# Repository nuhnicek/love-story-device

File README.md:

# GSM touch keychain (pair)

Press the button on one keychain and the other one vibrates and blinks, over 2G (SIM800L).

**Newest design: [`v3/`](v3/README.md)**, one custom 23 × 30 mm board with the nRF9151 (LTE-M), hand assembled.

**Module build: [`v2/`](v2/README.md)**, the module build: XIAO ESP32-C3 + SIM800L + 802530 LiPo, no custom PCB.
It has the parts list, schematic, case STLs/G-code and the relay backend.

v1 (custom PCB, ATtiny85):

- `hardware/` — carrier PCB (KiCad 10), parts list, cost estimate, gerbers, assembly files. Start at [hardware/README.md](hardware/README.md).
- `firmware/` — ATtiny85 firmware (1NCE GPRS → relay server), host unit tests.
- `server/` — relay server (Python, no dependencies) + tests + fake keychain for bring-up.
- `enclosure/` — 3D-printed case (OpenSCAD), heart perfboard layout, STLs and ready-to-print
  Ender-3 V2/Pro G-code.
- `.mcp.json` — project-scoped KiCad MCP servers (`mcp-server-kicad`: PCB + project tools).

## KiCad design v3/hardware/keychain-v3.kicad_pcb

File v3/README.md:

# GSM touch keychain, v3: one custom board with the nRF9151 (LTE-M)

v3 puts everything on **one 30 × 50 mm board** built around the **Nordic nRF9151**, including a
**heart of 18 RGB LEDs** and **programming over USB-C**. That
single chip holds the processor and the LTE-M/NB-IoT modem. There's no XIAO and no SIM800L,
and it's not affected by the 2G shutdown. You assemble it yourself.

| | v2 (modules) | **v3 (this)** |
|---|---|---|
| Network | 2G (SIM800L), ends for 1NCE ~end of 2027 | **LTE-M / NB-IoT** (4G), no 2G shutdown problem |
| Electronics | XIAO + SIM800L stacked, ~31 × 27 × 10 mm | **one 30 × 50 × ~4.5 mm board** with the RGB heart on it (USB-C is the tallest part) |
| Modem idle | ~1 mA (2G) | **µA level** with LTE-M power saving (PSM 2.7 µA, eDRX ~18 µA per Nordic) |
| Assembly | wires + through-hole | SMD: solder paste + stencil + hot plate (details below) |

**Guides:**
- [PROGRAMMING.md](PROGRAMMING.md): the first flash with a €5 Raspberry Pi Pico as the SWD probe (wiring + pyOCD), then updates over USB-C.
- [TESTING.md](TESTING.md): step-by-step checks of a freshly soldered board on the labelled test pads (bottom side), with the expected value at every pad.

## Files (`hardware/`)

| File | |
|---|---|
| `fab/schematic.pdf` | Schematic (A3). KiCad 10 project `keychain-v3.kicad_pro` |
| `keychain-v3.kicad_pcb` | The board: **4 layers, 1.0 mm**. ERC, DRC and schematic↔PCB parity are clean |
| `fab/keychain-v3-gerbers.zip` | **Upload this to JLCPCB** (all 4 copper layers, paste layers for the stencil, drills) |
| `fab/assembly-top.pdf`, `assembly-bottom.pdf` | Where every part goes, for hand placement |
| `fab/keychain-v3-pos-top.csv` | Part positions (only needed for machine assembly) |
| `BOM.md`, `fab/keychain-v3-bom.csv` | Parts list with suggested part numbers |
| `fab/keychain-v3.step`, `render-*.png` | 3D model for the case, pictures |
| `scripts/make_all.sh` | Regenerates everything: schematic → PCB → routing → checks → fab files |

## What's on the board

- **nRF9151** (U1):
  - Battery straight to VDD through a ferrite bead; no regulator needed (3.0–5.5 V).
  - The support parts follow Nordic's reference and the open-source Makerdiary nRF9151
    Connect Kit (CC BY-SA 4.0): 10 µF + 1 µF on VDD, 10 k ENABLE pull-up, 4.7 µF on DEC0,
    100 nF + 4.7 µF on VDD_GPIO, 1 k + 100 nF on reset.
- **3.0 V for the I/O pins** (U3, XC6206, 1 µA). It follows the battery up and down, which is the power-up order the nRF9151 requires.
- **Charger** (U2, TP4054) on USB-C:
  - **213 mA** (R3 = 4.7 k), which suits a 200–500 mAh cell. Use 3.3 k for 300 mA if the cell is at least 300 mAh.
  - "USB plugged in" goes to P0.31 (VBUS/2); with the battery voltage the firmware knows when it's charging.
- **Battery voltage** is measured by the modem itself (`AT%XVBAT`), so there are no divider resistors.
- **Nano-SIM** (J3, hinged holder on the bottom), with the ESD protection the SIM interface requires (U4).
  - U4 sits directly above the SIM contacts, as ESD protection should; its 100 nF (C13) is on the bottom next to the holder.
  - The nRF9151 runs SIMs at 1.8 V; 1NCE SIMs support that.
- **Antenna:**
  - A 50 Ω trace runs straight from the antenna pin to a **U.FL** socket.
  - It goes through a 0 Ω resistor and two unfitted pads (C14/C15) for later tuning.
  - Ground stitching vias around the socket; the 2nd layer is solid ground.
- **Motor:** AO3400A + flyback diode, the same as v1/v2, wired to the MOT+/− pads.
- **RGB heart (on the board):**
  - 18 × **Würth 1312020030000** (WL-ICLED, 2.0 × 2.0 mm, WS2812 protocol), each with its own 100 nF.
    - They sit on a 26 × 14 mm heart curve at the top of the board.
    - The parts are upright, evenly spaced and at least 0.3 mm apart. 18 is the most that fits on a 30 mm wide board; with 20, pads would touch on the curves.
    - In stock at DigiKey. Alternative: Dialight 587-1024-147F.
  - The load switch (U6, TPS22917) and the data buffer (U7, SN74LV1T34) sit inside the heart.
    - U6 cuts the LED power when they're dark. These LEDs draw ~1 mA each even when off, which would cost more than the whole keychain in standby.
    - U7 lifts the 3.0 V data to the LED supply.
  - The LEDs are fed by a heart-shaped copper plane on layer 3.
  - The data chain runs on the bottom layer, with a few links on top. Every link is collision-checked.
  - Any colour per LED and fades.
    - The LEDs are rated down to 3.3 V, so expect full colour down to ~3.3 V battery.
    - They take 5.5 mA per colour, so the whole heart at full white is ≈ 300 mA. The small LiPo handles that in short flashes.
  - Firmware: Zephyr `ws2812` driver with a reset time of ≥ 280 µs and a "1" pulse of ≈ 0.9 µs. The Würth datasheet allows 0.75–1.05 µs.
- **USB-C with data (CP2102N, U5):**
  - Firmware updates and the log go over USB-C. The SWD pads are needed only once, to install the bootloader.
  - The PC can reset the board through DTR/RTS (Q2, as on ESP32 boards). Idle, an open port and an unplugged cable never reset it.
  - The chip runs only from USB, so it costs no battery.
- **Side button** (SW1) on the right edge, pressed through the case's flexing tab.
- **Pads on the bottom:**
  - BAT+/−, MOT+/−;
  - **SWD** (CK, IO, RST, VT, GND), for the one-time bootloader flash.

Pins used: P0.05 motor PWM, P0.06 LED data, P0.19 LED power, P0.30 button, P0.31 USB plugged in, P0.24 UART TX, P0.25 UART RX (to the USB-serial chip)
(set these in the Zephyr devicetree; the nRF9151 can put the UART on any pin).

## Ordering

**PCB (JLCPCB):** upload `fab/keychain-v3-gerbers.zip` and choose:
- **4 layers, 1.0 mm**, impedance stack-up **JLC04101H-7628**. The antenna trace is sized for it (0.35 mm over layer 2). Check it in JLC's impedance calculator.
- **Surface finish: ENIG.** It isn't optional here: a flat finish matters for the nRF9151's pads underneath, and HASL is too uneven.
- Via covering: tented. Silkscreen: any colour.
- **Stencil:** order one with the PCB, **top side only, 0.10 mm thick**, framework-less is fine.

**Parts:** see `BOM.md`; LCSC, TME, Mouser or DigiKey all work. Order for **3 boards**, plus extra small parts.
- The **nRF9151-LACA** is the expensive part. It's sold as cut tape by DigiKey, Mouser and TME. Check the price; plan roughly €20–30 each.
- It's moisture sensitive (MSL 3): keep it in its sealed bag until you solder.

**Rough cost for a pair (+1 spare board):**

| Item | Approx. |
|---|---|
| PCB 4-layer ENIG × 5 + stencil + shipping to CZ | ~€35–60 |
| 3 × nRF9151 | ~€60–90 |
| Other parts for 3 boards (USB-C, SIM holder, U.FL, CP2102N, 30 RGB LEDs, ICs, passives) | ~€30–45 |
| 2 × LTE FPC antenna with U.FL | ~€5–20 |
| 2 × LiPo, 2 × motor, heart parts | ~€10–15 |
| 2 × 1NCE SIM | ~€24 |
| **Total** | **≈ €165–250 (≈ 4 100–6 200 Kč)** |

This is more than v2. You pay for the nRF9151 and a 4-layer ENIG board, and get LTE-M, much
lower standby current and a smaller keychain.

## Hand assembly

You need:
- **Hot plate**, about €25–40. Hot air works too, but a hot plate is easier for the nRF9151.
- **Solder paste:** Sn63/Pb37, the easiest to work with; or low-temperature paste.
- **Flux, fine tweezers,** a loupe or microscope, a multimeter, and isopropyl alcohol.
- **Current-limited bench supply** (optional, but very useful for the first power-up).

1. **Paste:**
   - Tape the board down with spare boards or scrap of the same thickness around it.
   - Line up the stencil and spread the paste in one stroke.
   - Check that every pad of the nRF9151, including the big centre ones, got paste.
2. **Place parts:**
   - Follow `assembly-top.pdf`. Start with the **nRF9151**, matching its pin-1 corner to the triangle on the silkscreen.
   - Then U2/U3/U4/Q1. Watch U4: it's tiny, and pin 1 has a dot.
   - Then the passives, USB-C, U.FL and SW1.
   - **Leave C14/C15 empty.**
3. **Reflow on the hot plate:**
   - Heat to ~150 °C for about a minute, then to the paste's peak: ~215–225 °C for Sn63, ~245 °C for lead-free.
   - Hold until all the paste has turned shiny, plus ~20 s.
   - Then slide the board off onto a metal surface.
   - Don't nudge the nRF9151 while hot: it self-centres on its pads.
4. **Inspect:**
   - Check for bridges on the USB-C, U2 and U4 with a loupe; fix them with flux + iron + solder wick.
   - You can't see under the nRF9151, so test it electrically (step 6).
5. **Bottom side, with an iron:**
   - The **SIM holder**: its contacts are on the outer edge, and the 4 shield tabs are at its sides.
   - C13 (100 nF, 0603) next to the holder.
   - Then the wires to the battery and the motor.
6. **First power-up, before connecting a battery:**
   - Put **3.8 V** on BAT+/− from a supply limited to ~100 mA. Idle current should be a few mA or less, with nothing getting warm.
   - **VT** should read **3.0 V**.
   - Then plug in USB-C: about 213 mA should flow into a battery.
7. **First flash, once, over SWD:**
   - Connect a debug probe to **CK/IO/RST/VT/GND**: a J-Link, the debug-out of an nRF9151 DK, or a borrowed / €5 Pico probe with pyOCD.
   - Flash the **MCUboot** bootloader together with the first app.
   - MCUboot is set to wait ~0.5 s after every reset for an update over the USB serial port.
8. **From then on, over USB-C only:**
   - The board shows up as a USB serial port (CP2102N). Log: any serial terminal at 115200.
   - Update: `mcumgr --conntype serial --connstring "dev=<port>,baud=115200" image upload app.bin`, then `reset`.
   - The PC resets the board by setting DTR high and RTS low. A small script in the firmware folder will do this.
   - LTE-M test: the `at_client` sample over USB, `AT+CFUN=1`, then `AT+CEREG?`. Registration status 1 or 5 means LTE-M works with the 1NCE SIM.

## Design review (2026-11-25)

DRC only proves the geometry is legal, so the board was also checked for design mistakes.
Found and fixed:

| Problem | Fix |
|---|---|
| Wide-track rules didn't apply to the nRF9151 supply and the motor line: the schematic names those nets `/VDD_NRF` and `/MOT_N`. VDD was routed 0.11 mm wide over 34 mm and 3 layers; the motor line went down to 0.09 mm | Rules match the real net names. VDD: 0.3 mm on the top layer only, fixed short track from pin 14 to C5/C6. Motor: 0.3 mm |
| Side button rotated the wrong way: actuator into the board, pads at the edge | Rotated 180°; the actuator now sticks 0.24 mm out of the right edge |
| Charger input and output caps (C1/C2) were 8.5 mm from the TP4054 | Charger block moved next to the battery pads; caps 2.7 and 4 mm from the pins |
| Signal and power vias under the nRF9151 | Keep-out while routing: only ground vias under the SiP, and layer 2 is solid ground there |
| SIM ESD (U4) and its 100 nF sat by the SiP, far from the SIM contacts | U4 moved directly above the contacts, with fixed short runs to each contact. The 100 nF is on the bottom next to the VCC contact |
| Several caps had their signal pad on the far side (C5, C6, C9, C10, C12) | Rotated; DEC0 cap 1.6 mm and VDD_GPIO 100 nF 1.9 mm from their pins |
| The two unfitted antenna pads would have got solder paste | Own footprint without stencil openings |
| Alternative charger part: the MCP73831 drives its status pin to 5 V, which would damage the nRF9151's 3.0 V pin | BOM now names the MCP73832 (open-drain status) |
| The left side of the SiP was too crowded to route cleanly | Board 2 mm wider. UART moved to P0.24/P0.25 and the debug pads put in pin order |

Checked and OK:
- every part's pinout against its footprint;
- the nRF9151 reference circuit;
- the USB-C front at the board edge;
- the RF path (no other copper near it, ground under and around it);
- the SIM holder's keep-out areas;
- 1.0 mm 4-layer stack-up, 0.3/0.6 mm vias, minimum track 0.11 mm (JLC 4-layer allows 0.09).

### Added after the review: USB programming and the RGB heart (2026-11-26)

- **USB corner:** laid out by pin order.
  - The CP2102N sits between the antenna socket and the button.
  - The reset transistor sits at its DTR/RTS pins; its caps and dividers sit at their pins.
- **Fixed routing:** the USB data pair is a fixed pair on layer 3, joined under the connector body so both plug orientations work.
- **Heart:** the LED chain runs on the bottom layer under the heart, and the LED supply is a plane on layer 3.
- **Hand-routed nets:** the SIM lines, reset, enable, the battery feed to the regulator and the LED data were drawn as fixed tracks, so the result doesn't depend on autorouter luck.
- **Charge status (CHRG):** dropped; the firmware uses *USB plugged in* plus the battery voltage instead.
- **Result:** ERC, DRC and schematic↔PCB parity are clean. The board is 30 × 50 mm and has 89 parts.
- **Test pads (added 2026-11-26):**
  - 12 labelled 0.9 mm pads on the bottom: 5V, V3U, DET, PRG, VDD, SIM, VLED, GATE, LED, BTN and 2 × GND.
  - Each one is wired with a fixed, collision-checked stub, so they don't depend on the autorouter.
  - See [TESTING.md](TESTING.md).

## Status and open points

- **Firmware: not written yet.**
  - v3 needs a Zephyr / nRF Connect SDK version of the keychain firmware.
  - The protocol (`firmware/keychain/protocol.h`) and the relay server (`v2/backend`) stay the same.
  - LTE-M power saving (eDRX) decides how fast incoming taps arrive (a few seconds to ~20 s) and how long the battery lasts. That gets tuned on the real board.
- **Modem firmware:** check the version with `AT%SHORTSWVER`. A brand-new chip already has modem firmware; later updates go through the app or `nrfutil` with a J-Link.
- **Antenna:**
  - LTE-M uses 800/900 MHz in Czechia, and antennas for those bands want length. A small flexible antenna inside a keychain will work, with reduced range.
  - Use the biggest one that fits; tuning with C14/C15 needs a network analyser.
- **1NCE LTE-M in Czechia** probably runs via T-Mobile CZ, but that isn't confirmed. Test one SIM first, e.g. on an M5Stamp CatM or an nRF9151 dev kit.
- **First build:**
  - This is a new design and hasn't been made yet. Order the spare SiP.
  - Hand-soldering an LGA chip is the hardest step, so expect one board to need rework.
- **Case:** not yet adapted to v3. Once you've picked the battery, the case can be redrawn around the 30 × 50 mm board: thinner than v2, with the heart under a translucent lid or light holes.

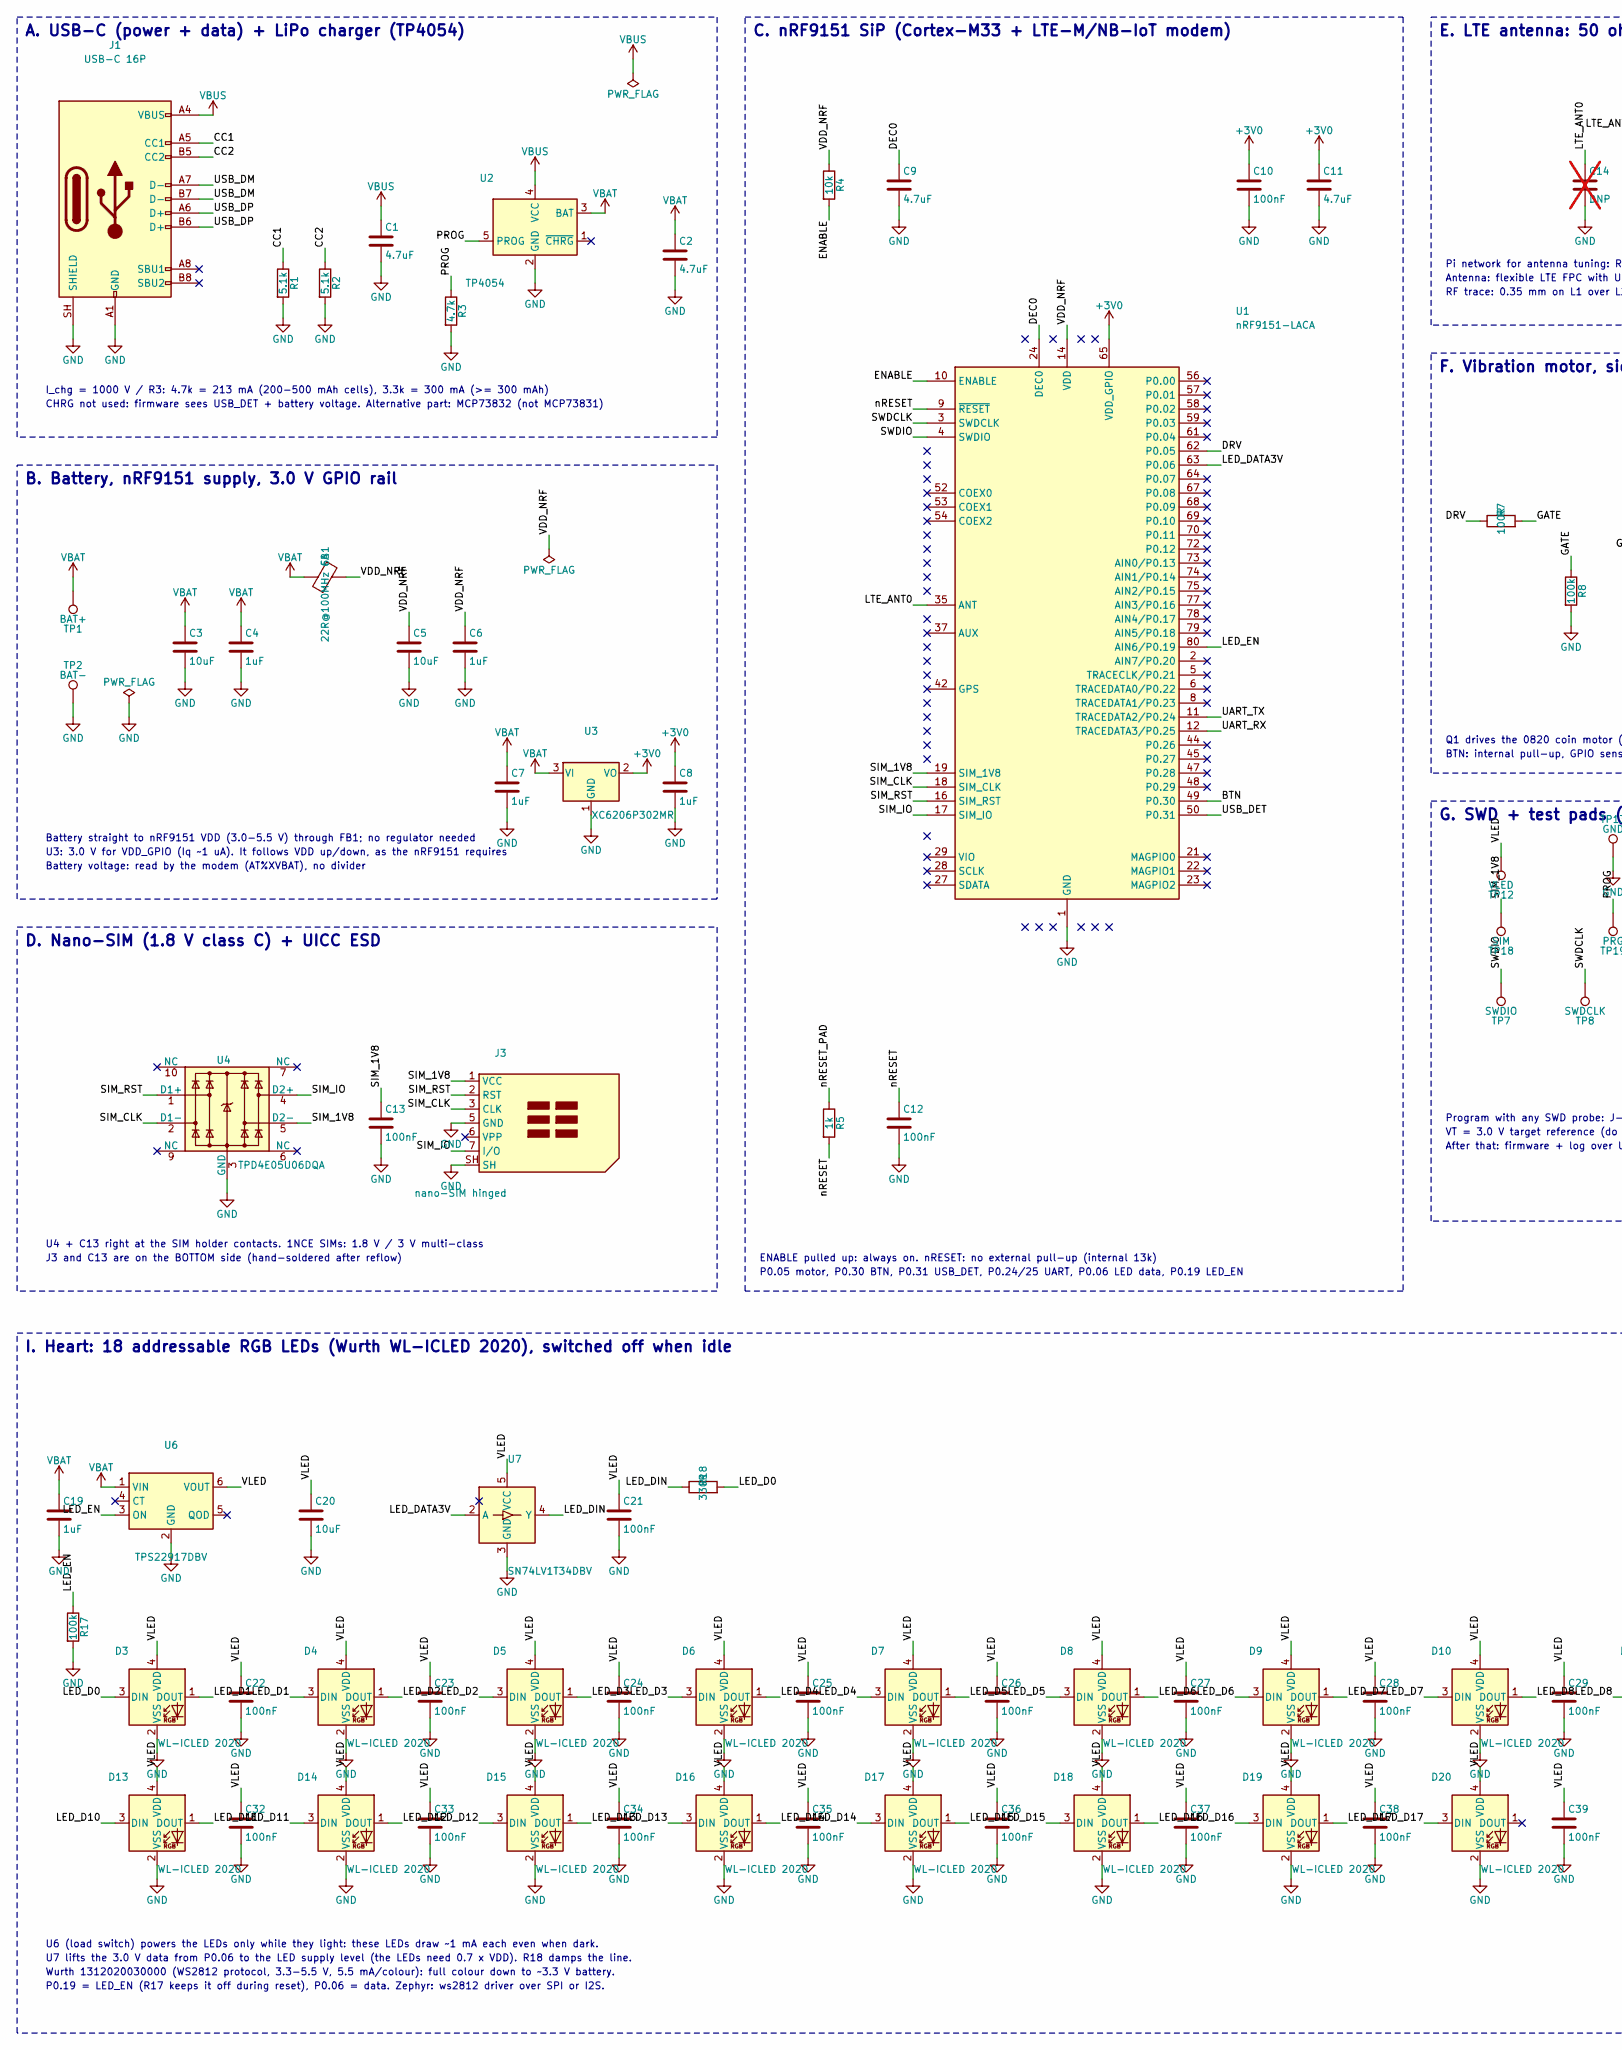
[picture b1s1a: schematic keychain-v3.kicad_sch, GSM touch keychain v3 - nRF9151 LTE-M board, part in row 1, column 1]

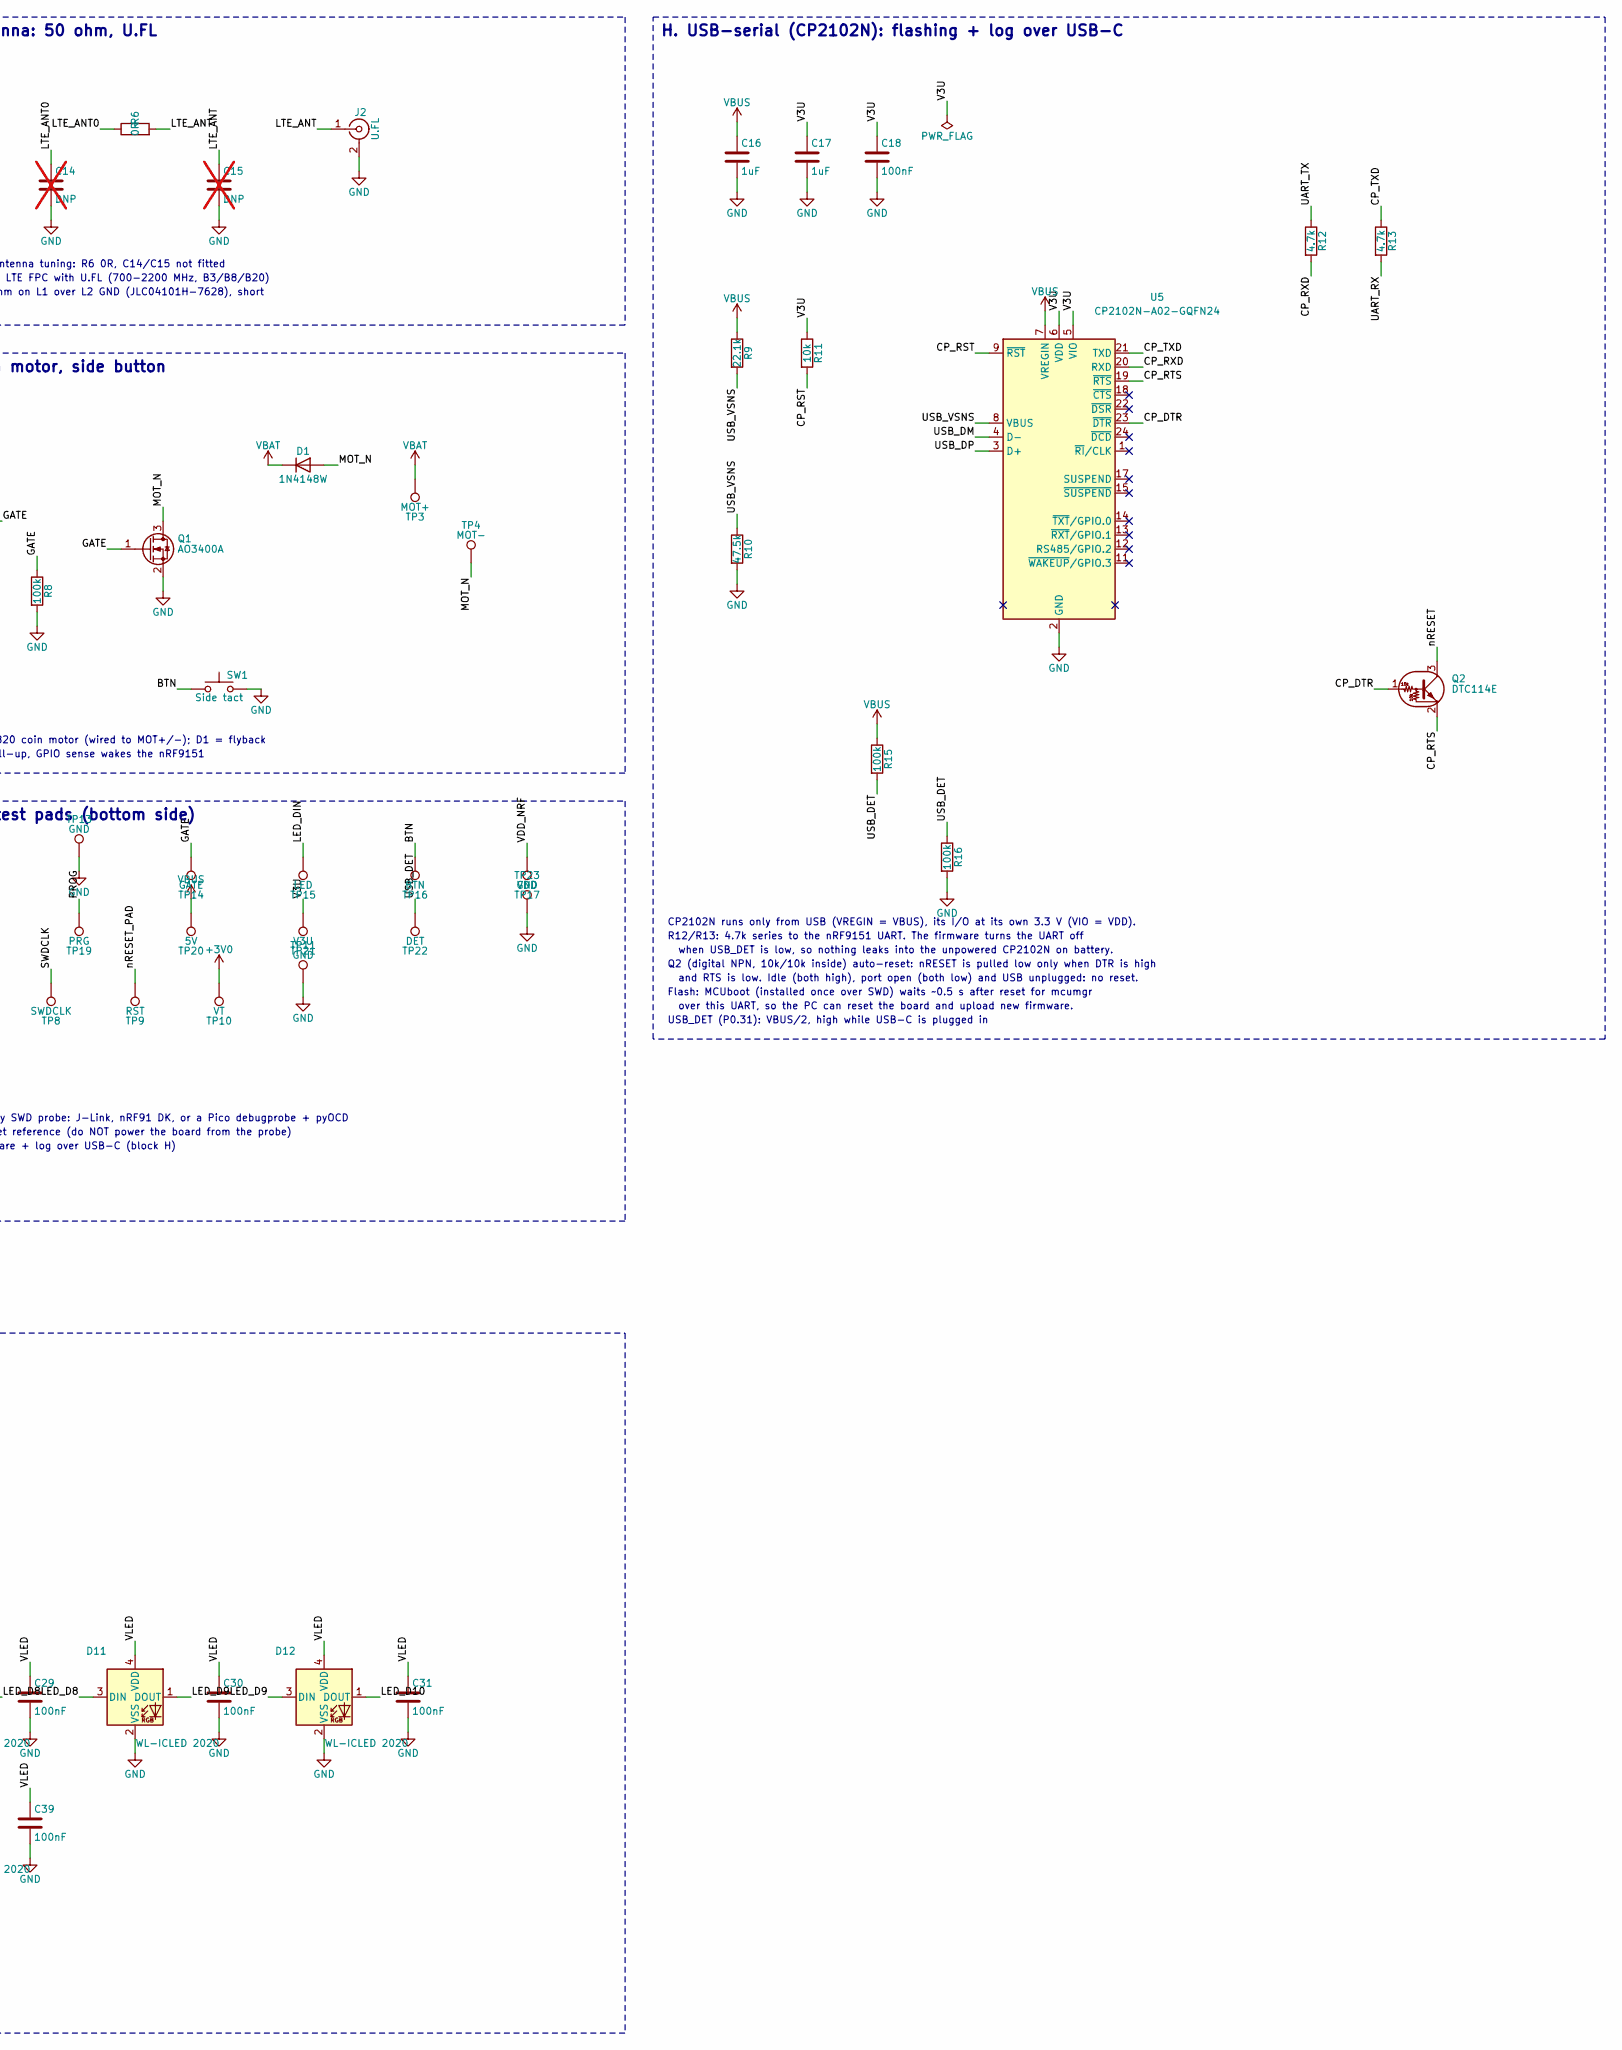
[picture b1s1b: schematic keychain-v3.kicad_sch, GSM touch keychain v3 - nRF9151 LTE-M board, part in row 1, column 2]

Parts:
C1, C2, C9, C11: 4.7uF; C_0603_1608Metric
C3, C5, C20: 10uF; C_0603_1608Metric
C4, C6, C7, C8: 1uF; C_0603_1608Metric
C10, C12, C13: 100nF; C_0603_1608Metric
C14, C15: DNP; C_0402_NoPaste; not fitted
C16, C17, C19: 1uF; C_0402_1005Metric
C18, C21, C22, C23, C24, C25, C26, C27, C28, C29, C30, C31, C32, C33, C34, C35, C36, C37, C38, C39: 100nF; C_0402_1005Metric
D1: 1N4148W; D_SOD-123
D3, D4, D5, D6, D7, D8, D9, D10, D11, D12, D13, D14, D15, D16, D17, D18, D19, D20: WL-ICLED 2020; LED_WL-ICLED_2020
FB1: 22R@100MHz 6A; L_0805_2012Metric
J1: USB-C 16P; USB_C_Receptacle_GCT_USB4105-xx-A_16P_TopMnt_Horizontal
J2: U.FL; U.FL_Hirose_U.FL-R-SMT-1_Vertical
J3: nano-SIM hinged; nanoSIM_GCT_SIM8060-6-0-14-00
Q1: AO3400A; SOT-23
Q2: DTC114E; SOT-23
R1, R2: 5.1k; R_0402_1005Metric
R3, R12, R13: 4.7k; R_0402_1005Metric
R4: 10k; R_0603_1608Metric
R5: 1k; R_0603_1608Metric
R6: 0R; R_0402_1005Metric
R7: 100R; R_0603_1608Metric
R8: 100k; R_0603_1608Metric
R9: 22.1k; R_0402_1005Metric
R10: 47.5k; R_0402_1005Metric
R11: 10k; R_0402_1005Metric
R15, R16, R17: 100k; R_0402_1005Metric
R18: 330R; R_0402_1005Metric
SW1: Side tact; SW_Push_1P1T-MP_NO_Horizontal_Alps_SKRTLAE010
TP1: BAT+; WirePad_1.5mm
TP2: BAT-; WirePad_1.5mm
TP3: MOT+; WirePad_1.0mm
TP4: MOT-; WirePad_1.0mm
TP7: SWDIO; WirePad_0.9mm
TP8: SWDCLK; WirePad_0.9mm
TP9: RST; WirePad_0.9mm
TP10: VT; WirePad_0.9mm
TP11, TP13, TP23: GND; WirePad_0.9mm
TP12: VLED; WirePad_0.9mm
TP14: GATE; WirePad_0.9mm
TP15: LED; WirePad_0.9mm
TP16: BTN; WirePad_0.9mm
TP17: VDD; WirePad_0.9mm
TP18: SIM; WirePad_0.9mm
TP19: PRG; WirePad_0.9mm
TP20: 5V; WirePad_0.9mm
TP21: V3U; WirePad_0.9mm
TP22: DET; WirePad_0.9mm
U1: nRF9151-LACA; Nordic_nRF9151-LAxx_LGA-80-33EP_12.1x11.1mm_P0.5mm
U2: TP4054; SOT-23-5
U3: XC6206P302MR; SOT-23-3
U4: TPD4E05U06DQA; USON-10_2.5x1.0mm_P0.5mm
U5: CP2102N-A02-GQFN24; QFN-24-1EP_4x4mm_P0.5mm_EP2.6x2.6mm
U6: TPS22917DBV; SOT-23-6
U7: SN74LV1T34DBV; SOT-23-5

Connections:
+3V0: C8.1, C10.1, C11.1, TP10.1, U1.65 (VDD_GPIO), U3.2 (VO)
/BTN: SW1.1, TP16.1, U1.49 (P0.30)
/CC1: J1.A5 (CC1), R1.1
/CC2: J1.B5 (CC2), R2.1
/CP_DTR: Q2.1 (B), U5.23 (~DTR)
/CP_RST: R11.2, U5.9 (~RST)
/CP_RTS: Q2.2 (E), U5.19 (~RTS)
/CP_RXD: R12.2, U5.20 (RXD)
/CP_TXD: R13.1, U5.21 (TXD)
/DEC0: C9.1, U1.24 (DEC0)
/DRV: R7.1, U1.62 (P0.05)
/ENABLE: R4.2, U1.10 (ENABLE)
/GATE: Q1.1 (G), R7.2, R8.1, TP14.1
/LED_D0: D3.3 (DIN), R18.2
/LED_D1: D3.1 (DOUT), D4.3 (DIN)
/LED_D2: D4.1 (DOUT), D5.3 (DIN)
/LED_D3: D5.1 (DOUT), D6.3 (DIN)
/LED_D4: D6.1 (DOUT), D7.3 (DIN)
/LED_D5: D7.1 (DOUT), D8.3 (DIN)
/LED_D6: D8.1 (DOUT), D9.3 (DIN)
/LED_D7: D9.1 (DOUT), D10.3 (DIN)
/LED_D8: D10.1 (DOUT), D11.3 (DIN)
/LED_D9: D11.1 (DOUT), D12.3 (DIN)
/LED_D10: D12.1 (DOUT), D13.3 (DIN)
/LED_D11: D13.1 (DOUT), D14.3 (DIN)
/LED_D12: D14.1 (DOUT), D15.3 (DIN)
/LED_D13: D15.1 (DOUT), D16.3 (DIN)
/LED_D14: D16.1 (DOUT), D17.3 (DIN)
/LED_D15: D17.1 (DOUT), D18.3 (DIN)
/LED_D16: D18.1 (DOUT), D19.3 (DIN)
/LED_D17: D19.1 (DOUT), D20.3 (DIN)
/LED_DATA3V: U1.63 (P0.06), U7.2 (A)
/LED_DIN: R18.1, TP15.1, U7.4 (Y)
/LED_EN: R17.1, U1.80 (AIN6/P0.19), U6.3 (ON)
/LTE_ANT: C15.1, J2.1 (In), R6.2
/LTE_ANT0: C14.1, R6.1, U1.35 (ANT)
/MOT_N: D1.2 (A), Q1.3 (D), TP4.1
/PROG: R3.1, TP19.1, U2.5 (PROG)
/SIM_1V8: C13.1, J3.1 (VCC), TP18.1, U1.19 (SIM_1V8), U4.5 (D2-)
/SIM_CLK: J3.3 (CLK), U1.18 (SIM_CLK), U4.2 (D1-)
/SIM_IO: J3.7 (I/O), U1.17 (SIM_IO), U4.4 (D2+)
/SIM_RST: J3.2 (RST), U1.16 (SIM_RST), U4.1 (D1+)
/SWDCLK: TP8.1, U1.3 (SWDCLK)
/SWDIO: TP7.1, U1.4 (SWDIO)
/UART_RX: R13.2, U1.12 (TRACEDATA3/P0.25)
/UART_TX: R12.1, U1.11 (TRACEDATA2/P0.24)
/USB_DET: R15.2, R16.1, TP22.1, U1.50 (P0.31)
/USB_DM: J1.A7 (D-), J1.B7 (D-), U5.4 (D-)
/USB_DP: J1.A6 (D+), J1.B6 (D+), U5.3 (D+)
/USB_VSNS: R9.2, R10.1, U5.8 (VBUS)
/V3U: C17.1, C18.1, R11.1, TP21.1, U5.5 (VIO), U5.6 (VDD)
/VDD_NRF: C5.1, C6.1, FB1.2, R4.1, TP17.1, U1.14 (VDD)
/VLED: C20.1, C21.1, C22.1, C23.1, C24.1, C25.1, C26.1, C27.1, C28.1, C29.1, C30.1, C31.1, C32.1, C33.1, C34.1, C35.1, C36.1, C37.1, C38.1, C39.1, D3.4 (VDD), D4.4 (VDD), D5.4 (VDD), D6.4 (VDD), D7.4 (VDD), D8.4 (VDD), D9.4 (VDD), D10.4 (VDD), D11.4 (VDD), D12.4 (VDD), D13.4 (VDD), D14.4 (VDD), D15.4 (VDD), D16.4 (VDD), D17.4 (VDD), D18.4 (VDD), D19.4 (VDD), D20.4 (VDD), TP12.1, U6.6 (VOUT), U7.5 (VCC)
/nRESET: C12.1, Q2.3 (C), R5.2, U1.9 (~RESET)
/nRESET_PAD: R5.1, TP9.1
GND: C1.2, C2.2, C3.2, C4.2, C5.2, C6.2, C7.2, C8.2, C9.2, C10.2, C11.2, C12.2, C13.2, C14.2, C15.2, C16.2, C17.2, C18.2, C19.2, C20.2, C21.2, C22.2, C23.2, C24.2, C25.2, C26.2, C27.2, C28.2, C29.2, C30.2, C31.2, C32.2, C33.2, C34.2, C35.2, C36.2, C37.2, C38.2, C39.2, D3.2 (VSS), D4.2 (VSS), D5.2 (VSS), D6.2 (VSS), D7.2 (VSS), D8.2 (VSS), D9.2 (VSS), D10.2 (VSS), D11.2 (VSS), D12.2 (VSS), D13.2 (VSS), D14.2 (VSS), D15.2 (VSS), D16.2 (VSS), D17.2 (VSS), D18.2 (VSS), D19.2 (VSS), D20.2 (VSS), J1.A1 (GND), J1.A12 (GND), J1.B1 (GND), J1.B12 (GND), J1.SH (SHIELD), J2.2 (Ext), J3.5 (GND), J3.SH, Q1.2 (S), R1.2, R2.2, R3.2, R8.2, R10.2, R16.2, R17.2, SW1.2, TP2.1, TP11.1, TP13.1, TP23.1, U1.1 (GND), U1.7 (GND), U1.13 (GND), U1.15 (GND), U1.20 (GND), U1.25 (GND), U1.30 (GND), U1.34 (GND), U1.36 (GND), U1.38 (GND), U1.39 (GND), U1.40 (GND), U1.41 (GND), U1.43 (GND), U1.46 (GND), U1.51 (GND), U1.55 (GND), U1.60 (GND), U1.66 (GND), U1.71 (GND), U1.76 (GND), U1.105 (GND), U1.106 (GND), U1.107 (GND), U1.108 (GND), U1.109 (GND), U1.110 (GND), U1.111 (GND), U1.112 (GND), U1.113 (GND), U2.2 (GND), U3.1 (GND), U4.3 (GND), U4.8 (GND), U5.2 (GND), U5.25 (GND), U6.2 (GND), U7.3 (GND)
VBAT: C2.1, C3.1, C4.1, C7.1, C19.1, D1.1 (K), FB1.1, TP1.1, TP3.1, U2.3 (BAT), U3.3 (VI), U6.1 (VIN)
VBUS: C1.1, C16.1, J1.A4 (VBUS), J1.A9 (VBUS), J1.B4 (VBUS), J1.B9 (VBUS), R9.1, R15.1, TP20.1, U2.4 (VCC), U5.7 (VREGIN)

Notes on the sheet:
A. USB-C (power + data) + LiPo charger (TP4054)
I_chg = 1000 V / R3: 4.7k = 213 mA (200-500 mAh cells), 3.3k = 300 mA (>= 300 mAh)
CHRG not used: firmware sees USB_DET + battery voltage. Alternative part: MCP73832 (not MCP73831)
B. Battery, nRF9151 supply, 3.0 V GPIO rail
Battery straight to nRF9151 VDD (3.0-5.5 V) through FB1; no regulator needed
U3: 3.0 V for VDD_GPIO (Iq ~1 uA). It follows VDD up/down, as the nRF9151 requires
Battery voltage: read by the modem (AT%XVBAT), no divider
C. nRF9151 SiP (Cortex-M33 + LTE-M/NB-IoT modem)
ENABLE pulled up: always on. nRESET: no external pull-up (internal 13k)
P0.05 motor, P0.30 BTN, P0.31 USB_DET, P0.24/25 UART, P0.06 LED data, P0.19 LED_EN
D. Nano-SIM (1.8 V class C) + UICC ESD
U4 + C13 right at the SIM holder contacts. 1NCE SIMs: 1.8 V / 3 V multi-class
J3 and C13 are on the BOTTOM side (hand-soldered after reflow)
E. LTE antenna: 50 ohm, U.FL
Pi network for antenna tuning: R6 0R, C14/C15 not fitted
Antenna: flexible LTE FPC with U.FL (700-2200 MHz, B3/B8/B20)
RF trace: 0.35 mm on L1 over L2 GND (JLC04101H-7628), short
F. Vibration motor, side button
Q1 drives the 0820 coin motor (wired to MOT+/-); D1 = flyback
BTN: internal pull-up, GPIO sense wakes the nRF9151
G. SWD + test pads (bottom side)
Program with any SWD probe: J-Link, nRF91 DK, or a Pico debugprobe + pyOCD
VT = 3.0 V target reference (do NOT power the board from the probe)
After that: firmware + log over USB-C (block H)
H. USB-serial (CP2102N): flashing + log over USB-C
CP2102N runs only from USB (VREGIN = VBUS), its I/O at its own 3.3 V (VIO = VDD).
R12/R13: 4.7k series to the nRF9151 UART. The firmware turns the UART off
when USB_DET is low, so nothing leaks into the unpowered CP2102N on battery.
Q2 (digital NPN, 10k/10k inside) auto-reset: nRESET is pulled low only when DTR is high
and RTS is low. Idle (both high), port open (both low) and USB unplugged: no reset.
Flash: MCUboot (installed once over SWD) waits ~0.5 s after reset for mcumgr
over this UART, so the PC can reset the board and upload new firmware.
USB_DET (P0.31): VBUS/2, high while USB-C is plugged in
I. Heart: 18 addressable RGB LEDs (Wurth WL-ICLED 2020), switched off when idle
U6 (load switch) powers the LEDs only while they light: these LEDs draw ~1 mA each even when dark.
U7 lifts the 3.0 V data from P0.06 to the LED supply level (the LEDs need 0.7 x VDD). R18 damps the line.
Wurth 1312020030000 (WS2812 protocol, 3.3-5.5 V, 5.5 mA/colour): full colour down to ~3.3 V battery.
P0.19 = LED_EN (R17 keeps it off during reset), P0.06 = data. Zephyr: ws2812 driver over SPI or I2S.

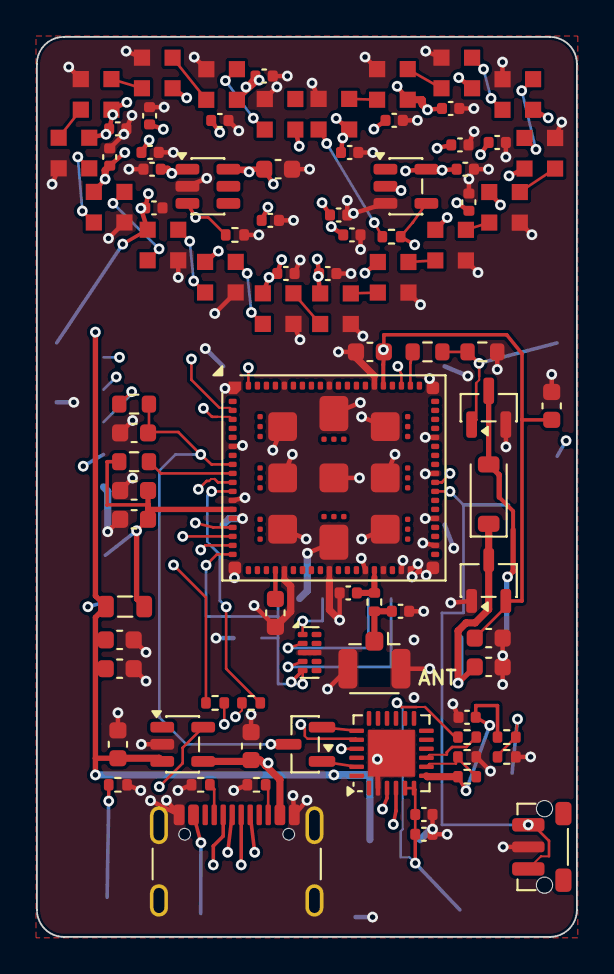
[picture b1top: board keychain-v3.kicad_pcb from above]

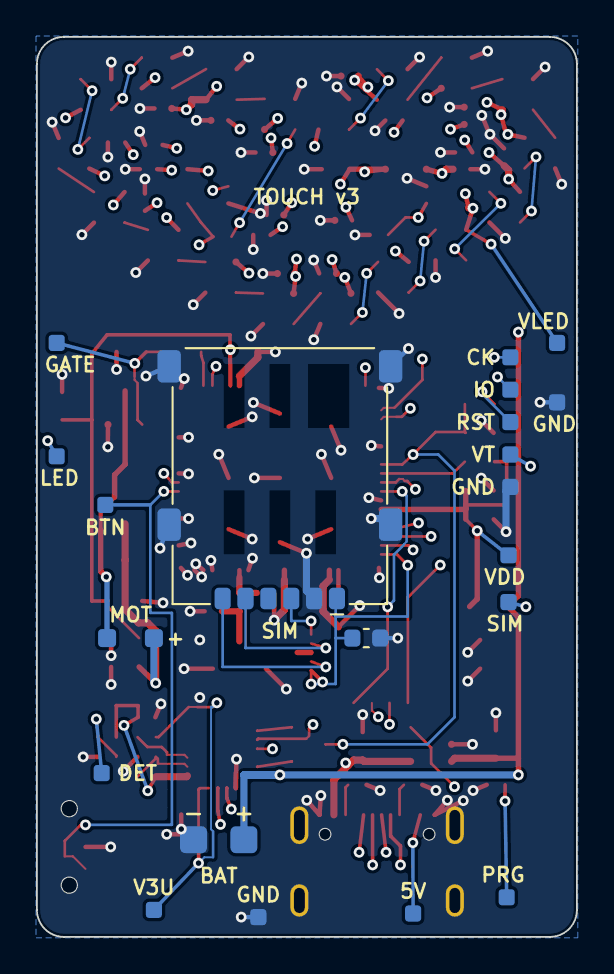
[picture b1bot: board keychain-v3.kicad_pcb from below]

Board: 4 copper layers, 30.0 x 50.0 mm, 110 parts (23 on the bottom side), 58 nets.

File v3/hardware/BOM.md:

# keychain v3: parts list

Generated by `scripts/bom.py` from the board. Quantities are per board; **order for 3 boards**
(a pair + one spare) and extra passives, they get lost under tweezers.

| Designators | Qty | Value | Package | Side | Description | Suggested MPN |
|---|---|---|---|---|---|---|
| C1, C2, C9, C11 | 4 | 4.7uF | C_0603 | top | MLCC 4.7 uF 10 V X5R 0603 | Samsung CL10A475KP8NNNC |
| C3, C5, C20 | 3 | 10uF | C_0603 | top | MLCC 10 uF 10 V X5R 0603 | Samsung CL10A106KP8NNNC |
| C4, C6, C7, C8 | 4 | 1uF | C_0603 | top | MLCC 1 uF 16 V X5R 0603 | Samsung CL10A105KO8NNNC |
| C10, C12, C13 | 3 | 100nF | C_0603 | bottom/top | MLCC 100 nF 16 V X7R 0603 | Samsung CL10B104KO8NNNC |
| C14, C15 | 2 | DNP (not fitted) | C_0402_NoPaste | top | Antenna tuning pad, NOT fitted (0402) | - |
| C16, C17, C19 | 3 | 1uF | C_0402 | top | MLCC 1 uF 25 V X5R 0402 | Samsung CL05A105KA5NNNC |
| C18, C21, C22, C23, C24, C25, C26, C27, C28, C29, C30, C31, C32, C33, C34, C35, C36, C37, C38, C39 | 20 | 100nF | C_0402 | top | MLCC 100 nF 16 V X7R 0402 | Samsung CL05B104KO5NNNC |
| D1 | 1 | 1N4148W | D_SOD-123 | top | Switching diode, SOD-123 (motor flyback) | Diodes 1N4148W-7-F |
| D3, D4, D5, D6, D7, D8, D9, D10, D11, D12, D13, D14, D15, D16, D17, D18, D19, D20 | 18 | WL-ICLED 2020 | LED_WL-ICLED_2020 | top | Addressable RGB LED 2.0 x 2.0 mm, WS2812 protocol, 3.3-5.5 V, 5.5 mA/colour (heart) | Wurth 1312020030000 (DigiKey 732-1312020030000CT-ND); alt. Dialight 587-1024-147F |
| FB1 | 1 | 22R@100MHz 6A | L_0805 | top | Ferrite bead 22 ohm @ 100 MHz, 6 A, 0805 (nRF9151 VDD) | Murata BLM21PG220SN1D |
| J1 | 1 | USB-C 16P | USB_C_Receptacle_GCT_USB4105-xx-A_16P_TopMnt_Horizontal | top | USB-C receptacle, USB 2.0, 16 pin, top mount | GCT USB4105-GF-A |
| J2 | 1 | U.FL | U.FL_Hirose_U.FL-R-SMT-1_Vertical | top | U.FL coaxial receptacle for the LTE antenna | Hirose U.FL-R-SMT-1(10) |
| J3 | 1 | nano-SIM hinged | nanoSIM_GCT_SIM8060-6-0-14-00 | bottom | Nano-SIM holder, hinged, 6 contacts (bottom side) | GCT SIM8060-6-0-14-00 |
| Q1 | 1 | AO3400A | SOT-23 | top | N-MOSFET 30 V 5.7 A, SOT-23 (motor + heart driver) | AOS AO3400A |
| Q2 | 1 | DTC114E | SOT-23 | top | Digital NPN 10k/10k, SOT-23 (USB auto-reset) | Rohm DTC114EKAT146 or Nexperia PDTC114ET |
| R1, R2 | 2 | 5.1k | R_0402 | top | Resistor 5.1k 1% 0402 (USB-C CC) | UNI-ROYAL 0402WGF5101TCE |
| R3, R12, R13 | 3 | 4.7k | R_0402 | top | Resistor 4.7k 1% 0402 (UART series; charge current: 4.7 k = 213 mA, 3.3 k = 300 mA) | UNI-ROYAL 0402WGF4701TCE |
| R4 | 1 | 10k | R_0603 | top | Resistor 10k 1% 0603 (ENABLE pull-up) | UNI-ROYAL 0603WAF1002T5E |
| R5 | 1 | 1k | R_0603 | top | Resistor 1k 1% 0603 (reset series) | UNI-ROYAL 0603WAF1001T5E |
| R6 | 1 | 0R | R_0402 | top | Resistor 0R 1% 0402 (antenna series) | UNI-ROYAL 0402WGF0000TCE |
| R7 | 1 | 100R | R_0603 | top | Resistor 100R 1% 0603 (motor gate) | UNI-ROYAL 0603WAF1000T5E |
| R8 | 1 | 100k | R_0603 | top | Resistor 100k 1% 0603 (gate pull-down) | UNI-ROYAL 0603WAF1003T5E |
| R9 | 1 | 22.1k | R_0402 | top | Resistor 22.1k 1% 0402 (VBUS sense divider) | UNI-ROYAL 0402WGF2212TCE |
| R10 | 1 | 47.5k | R_0402 | top | Resistor 47.5k 1% 0402 (VBUS sense divider) | UNI-ROYAL 0402WGF4752TCE |
| R11 | 1 | 10k | R_0402 | top | Resistor 10k 1% 0402 (CP2102N reset pull-up) | UNI-ROYAL 0402WGF1002TCE |
| R15, R16, R17 | 3 | 100k | R_0402 | top | Resistor 100k 1% 0402 (LED_EN pull-down; USB_DET divider) | UNI-ROYAL 0402WGF1003TCE |
| R18 | 1 | 330R | R_0402 | top | Resistor 330R 1% 0402 (LED data line) | UNI-ROYAL 0402WGF3300TCE |
| SW1 | 1 | Side tact | SW_Push_1P1T-MP_NO_Horizontal_Alps_SKRTLAE010 | top | Side-push tactile switch 3.5 x 2.9 mm | Alps SKRTLAE010 |
| U1 | 1 | nRF9151-LACA | Nordic_nRF9151-LAxx_LGA-80-33EP_12.1x11.1mm_P0.5mm | top | Nordic nRF9151 SiP: Cortex-M33 + LTE-M/NB-IoT modem + GNSS, LGA-80 12.1 x 11.1 mm | Nordic nRF9151-LACA (cut tape: nRF9151-LACA-R7) |
| U2 | 1 | TP4054 | SOT-23-5 | top | Li-ion/LiPo linear charger 4.2 V, SOT-23-5 (MCP73831 pinout), I = 1000 V / R3 | TP4054 (Nanjing Top Power) or MCP73832T-2ACI/OT (open-drain STAT; NOT the MCP73831, its STAT drives 5 V into the nRF9151) |
| U3 | 1 | XC6206P302MR | SOT-23-3 | top | LDO 3.0 V 200 mA, Iq 1 uA, SOT-23 (VDD_GPIO) | Torex XC6206P302MR |
| U4 | 1 | TPD4E05U06DQA | USON-10_2.5x1.0mm_P0.5mm | top | 4-channel ESD array for the SIM lines, USON-10 2.5 x 1 mm | TI TPD4E05U06DQAR |
| U5 | 1 | CP2102N-A02-GQFN24 | QFN-24-1EP_4x4mm_P0.5mm_EP2.6x2.6mm | top | USB-UART bridge, QFN-24 4 x 4 (firmware updates + log over USB-C) | Silicon Labs CP2102N-A02-GQFN24R |
| U6 | 1 | TPS22917DBV | SOT-23-6 | top | Load switch 1-5.5 V, SOT-23-6 (LED power off when idle) | TI TPS22917DBVR |
| U7 | 1 | SN74LV1T34DBV | SOT-23-5 | top | Single buffer / level shifter, SOT-23-5 (LED data 3.0 V -> VLED) | TI SN74LV1T34DBVR |

## Off-board parts (per pair)

| Connects to | Qty | Part |
|---|---|---|
| BAT+/BAT- | 2 | LiPo 3.7 V with protection PCM: 502025 (~200 mAh, 5 x 20 x 25) or 802530 (~500 mAh) |
| J2 | 2 | LTE flexible FPC antenna, 698-2200 MHz (B3/B8/B20), as large as the case allows; cable plug must be U.FL = IPEX MHF1 (NOT MHF4, which looks similar but is smaller) |
| J3 | 2 | 1NCE IoT SIM, nano size (1.8 V capable) |
| MOT+/- | 2 | 0820 coin vibration motor, 3 V |

Pads on the bottom side: BAT+/-, MOT+/- (wires), SWD (CK, IO, RST, VT, GND; first flash, see
../PROGRAMMING.md) and 12 labelled test pads (see ../TESTING.md). Firmware updates and the log go over USB-C.
